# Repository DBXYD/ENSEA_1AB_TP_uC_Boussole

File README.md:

# ENSEA_1AB_TP_uC_Boussole

## TP

### PCB
Composants : 
* [NUCLEO-L476RG](https://www.st.com/en/evaluation-tools/nucleo-l476rg.html)
* [Magnétomètre 3 axes MMC5603 ADA5579](https://www.gotronic.fr/art-magnetometre-3-axes-mmc5603-ada5579-35829.htm)
* [GPS Tel0094](https://www.gotronic.fr/art-module-gps-tel0094-25732.htm)
* [Microcontroleur pour simulation trame NMEA STM32C011J4M6](https://fr.farnell.com/stmicroelectronics/stm32c011j4m6/mcu-arm-32-bits-48mhz-nsoic-8/dp/4138300)
* [Moteur pas à pas 17hs15-0404s](https://www.gotronic.fr/art-moteur-17hs15-0404s-18354.htm)
* [Driver de moteur pas à pas TMC2225](https://fr.farnell.com/trinamic/tmc2225-sa-t/driver-de-moteur-2a-40-a-125-c/dp/3690353?st=TMC2225-SA-T)
* [Codeur rotatif](https://fr.farnell.com/bourns/pec12r-2220f-s0024/encoder-quadrature-24ppr-15rpm/dp/4014827)
* [Ecran OLED 0.96"](https://www.gotronic.fr/art-afficheur-oled-0-96-i2c-oled01-31506.htm)
* [Mesure de courant NCS199A3RSQT2G](https://fr.farnell.com/on-semiconductor/ncs199a3rsqt2g/ampli-musure-de-cour-40khz-40/dp/2981170?st=NCS199A3RSQT2G)

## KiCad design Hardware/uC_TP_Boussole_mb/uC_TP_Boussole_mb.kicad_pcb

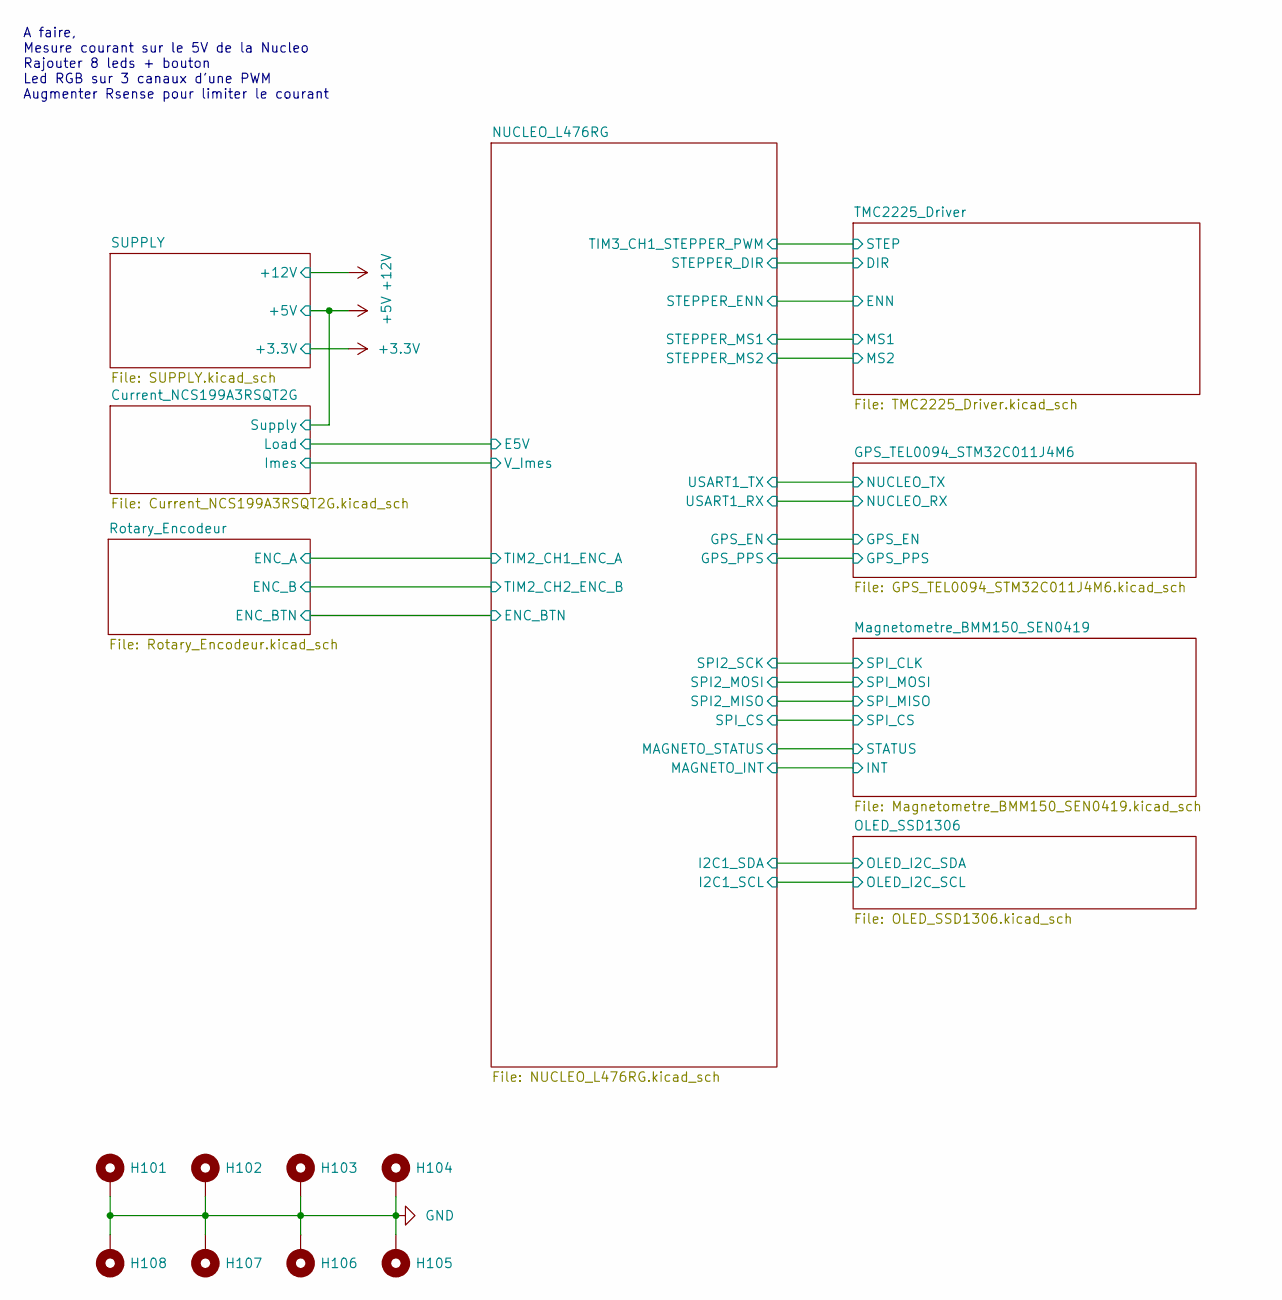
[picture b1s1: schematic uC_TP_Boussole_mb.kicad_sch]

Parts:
H101, H102, H103, H104, H105, H106, H107, H108: MountingHole_Pad; MountingHole_3.2mm_M3_Pad

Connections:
GND: H101.1, H102.1, H103.1, H104.1, H105.1, H106.1, H107.1, H108.1; also elsewhere on the board

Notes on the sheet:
A faire, Mesure courant sur le 5V de la Nucleo Rajouter 8 leds + bouton Led RGB sur 3 canaux d'une PWM Augmenter Rsense pour limiter le courant

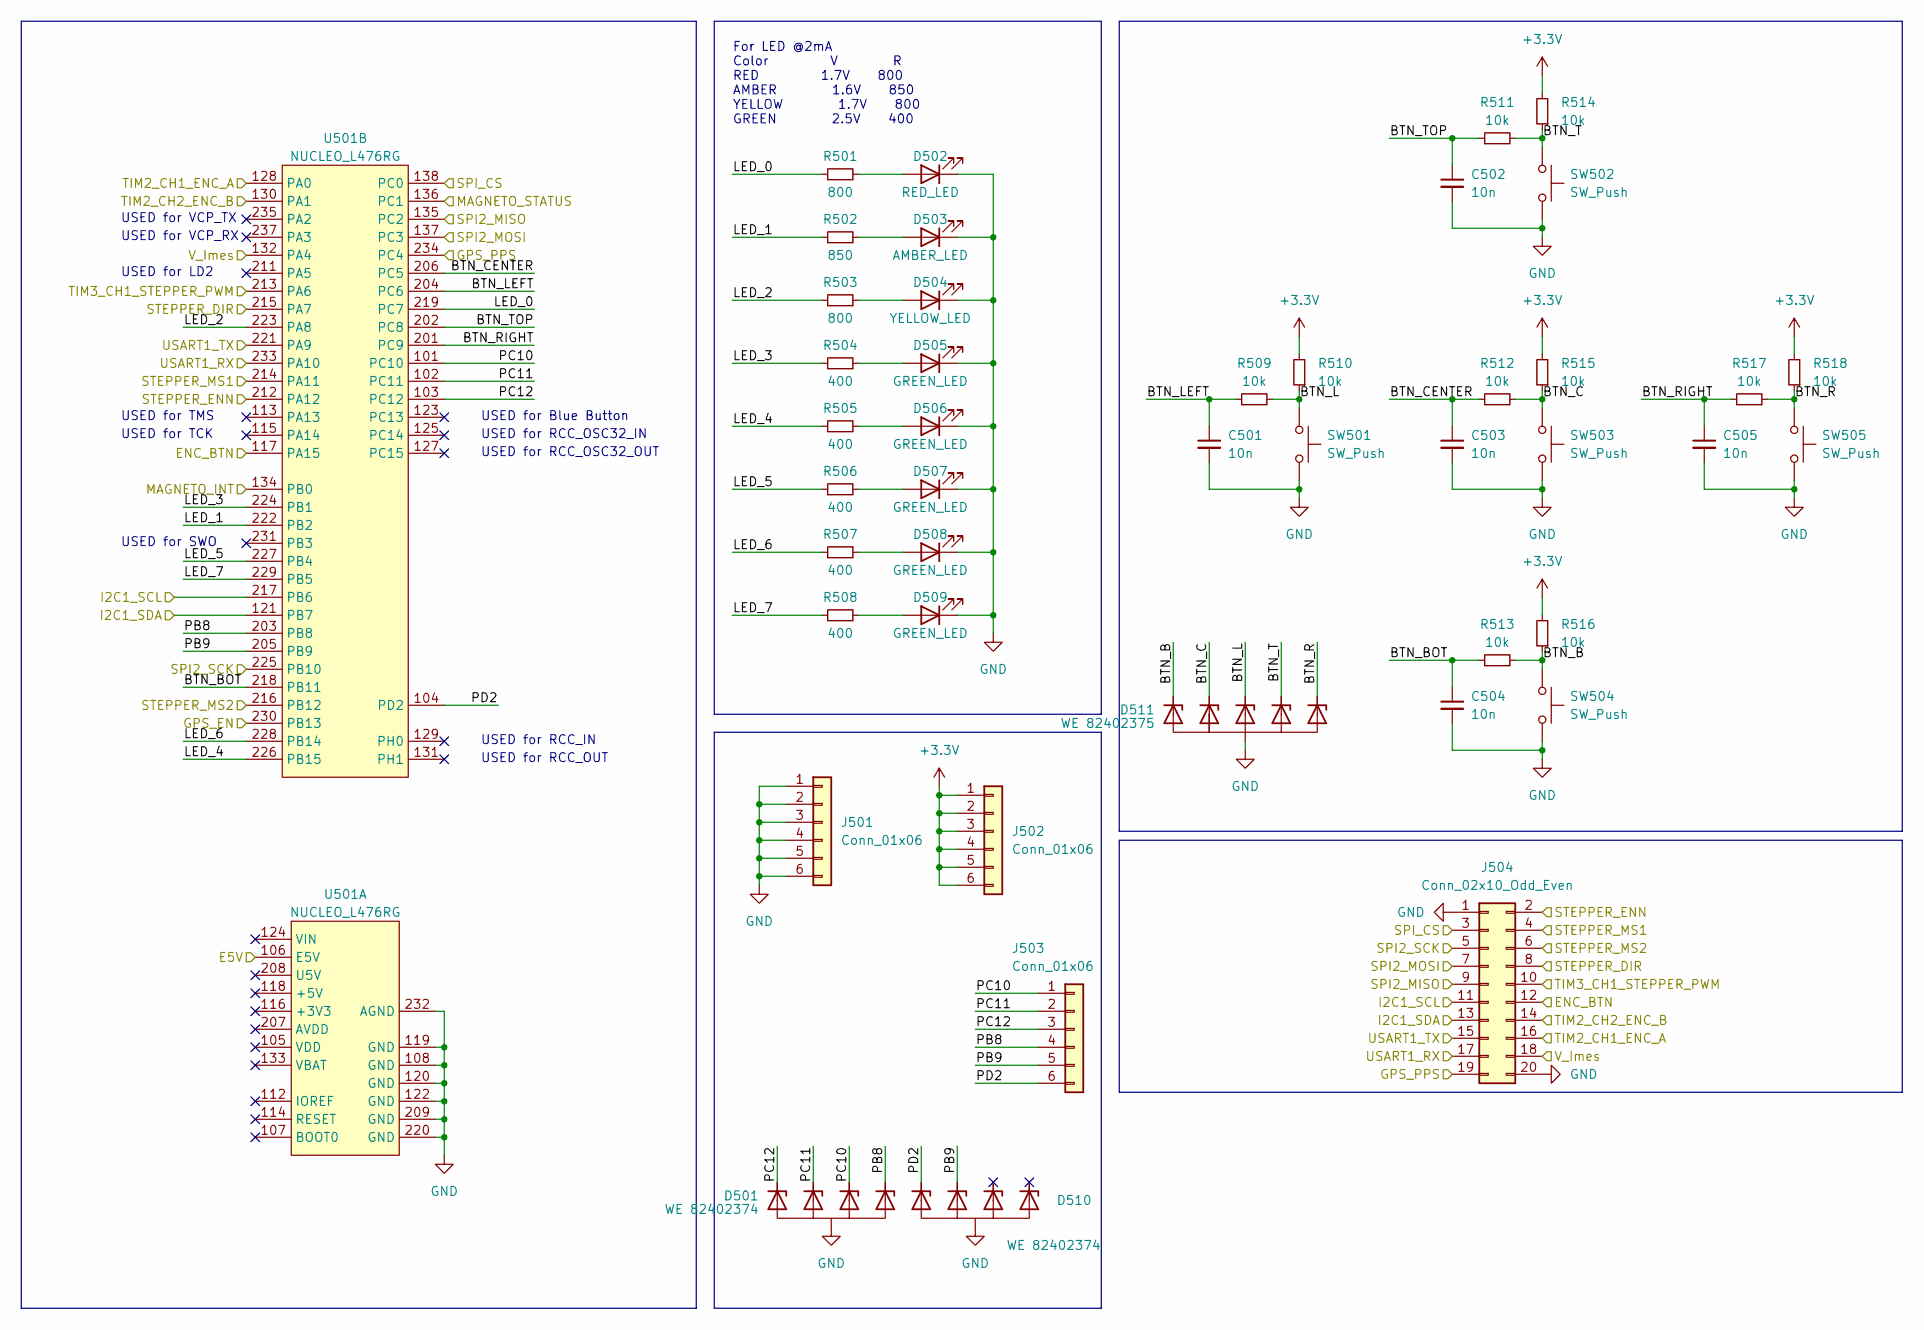
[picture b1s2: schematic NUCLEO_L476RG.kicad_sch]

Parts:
C501, C502, C503, C504, C505: 10n; C_0402_1005Metric
D501, D510: WE 82402374; SC70-5L; MPN WE 82402374
D502: RED_LED; LED_0603_1608Metric; MPN 150060RS55040
D503: AMBER_LED; LED_0603_1608Metric; MPN 150060AS55040
D504: YELLOW_LED; LED_0603_1608Metric; MPN 150060YS55040
D505, D506, D507, D508, D509: GREEN_LED; LED_0603_1608Metric; MPN 150060GS55040
D511: WE 82402375; SC70-6L; MPN WE 82402375
J501, J502, J503: Conn_01x06; PinHeader_1x06_P2.54mm_Vertical
J504: Conn_02x10_Odd_Even; PinHeader_2x10_P2.54mm_Vertical_SMD; MPN 61002021121
R501, R503: 800; R_0402_1005Metric
R502: 850; R_0402_1005Metric
R504, R505, R506, R507, R508: 400; R_0402_1005Metric
R509, R510, R511, R512, R513, R514, R515, R516, R517, R518: 10k; R_0402_1005Metric
SW501, SW502, SW503, SW504, SW505: SW_Push; SW_Push_1P1T_NO_6x6mm_H9.5mm
U501: NUCLEO_L476RG; ST_NUCLEO_64

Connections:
+3.3V: J502.1, J502.2, J502.3, J502.4, J502.5, J502.6, R510.2, R514.2, R515.2, R516.2, R518.2; also elsewhere on the board
/Current_NCS199A3RSQT2G/Imes: J504.18, U501.132 (PA4); also elsewhere on the board
/Current_NCS199A3RSQT2G/Load: U501.106 (E5V); also elsewhere on the board
/GPS_TEL0094_STM32C011J4M6/GPS_EN: U501.230 (PB13); also elsewhere on the board
/GPS_TEL0094_STM32C011J4M6/GPS_PPS: J504.19, U501.234 (PC4); also elsewhere on the board
/GPS_TEL0094_STM32C011J4M6/NUCLEO_RX: J504.17, U501.233 (PA10); also elsewhere on the board
/GPS_TEL0094_STM32C011J4M6/NUCLEO_TX: J504.15, U501.221 (PA9); also elsewhere on the board
/Magnetometre_BMM150_SEN0419/INT: U501.134 (PB0); also elsewhere on the board
/Magnetometre_BMM150_SEN0419/SPI_CLK: J504.5, U501.225 (PB10); also elsewhere on the board
/Magnetometre_BMM150_SEN0419/SPI_CS: J504.3, U501.138 (PC0); also elsewhere on the board
/Magnetometre_BMM150_SEN0419/SPI_MISO: J504.9, U501.135 (PC2); also elsewhere on the board
/Magnetometre_BMM150_SEN0419/SPI_MOSI: J504.7, U501.137 (PC3); also elsewhere on the board
/Magnetometre_BMM150_SEN0419/STATUS: U501.136 (PC1); also elsewhere on the board
/NUCLEO_L476RG/BTN_B: D511.6 (I/O), R513.2, R516.1, SW504.1
/NUCLEO_L476RG/BTN_BOT: C504.1, R513.1, U501.218 (PB11)
/NUCLEO_L476RG/BTN_C: D511.5 (I/O), R512.2, R515.1, SW503.1
/NUCLEO_L476RG/BTN_CENTER: C503.1, R512.1, U501.206 (PC5)
/NUCLEO_L476RG/BTN_L: D511.4 (I/O), R509.2, R510.1, SW501.1
/NUCLEO_L476RG/BTN_LEFT: C501.1, R509.1, U501.204 (PC6)
/NUCLEO_L476RG/BTN_R: D511.1 (I/O), R517.2, R518.1, SW505.1
/NUCLEO_L476RG/BTN_RIGHT: C505.1, R517.1, U501.201 (PC9)
/NUCLEO_L476RG/BTN_T: D511.3 (I/O), R511.2, R514.1, SW502.1
/NUCLEO_L476RG/BTN_TOP: C502.1, R511.1, U501.202 (PC8)
/NUCLEO_L476RG/ENC_BTN: J504.12, U501.117 (PA15); also elsewhere on the board
/NUCLEO_L476RG/I2C1_SCL: J504.11, U501.217 (PB6); also elsewhere on the board
/NUCLEO_L476RG/I2C1_SDA: J504.13, U501.121 (PB7); also elsewhere on the board
/NUCLEO_L476RG/LED_0: R501.1, U501.219 (PC7)
/NUCLEO_L476RG/LED_1: R502.1, U501.222 (PB2)
/NUCLEO_L476RG/LED_2: R503.1, U501.223 (PA8)
/NUCLEO_L476RG/LED_3: R504.1, U501.224 (PB1)
/NUCLEO_L476RG/LED_4: R505.1, U501.226 (PB15)
/NUCLEO_L476RG/LED_5: R506.1, U501.227 (PB4)
/NUCLEO_L476RG/LED_6: R507.1, U501.228 (PB14)
/NUCLEO_L476RG/LED_7: R508.1, U501.229 (PB5)
/NUCLEO_L476RG/PB8: D501.1 (I/O), J503.4, U501.203 (PB8)
/NUCLEO_L476RG/PB9: D510.4 (I/O), J503.5, U501.205 (PB9)
/NUCLEO_L476RG/PC10: D501.3 (I/O), J503.1, U501.101 (PC10)
/NUCLEO_L476RG/PC11: D501.4 (I/O), J503.2, U501.102 (PC11)
/NUCLEO_L476RG/PC12: D501.5 (I/O), J503.3, U501.103 (PC12)
/NUCLEO_L476RG/PD2: D510.5 (I/O), J503.6, U501.104 (PD2)
/NUCLEO_L476RG/STEPPER_DIR: J504.8, U501.215 (PA7); also elsewhere on the board
/NUCLEO_L476RG/STEPPER_ENN: J504.2, U501.212 (PA12); also elsewhere on the board
/NUCLEO_L476RG/STEPPER_MS1: J504.4, U501.214 (PA11); also elsewhere on the board
/NUCLEO_L476RG/STEPPER_MS2: J504.6, U501.216 (PB12); also elsewhere on the board
/NUCLEO_L476RG/TIM2_CH1_ENC_A: J504.16, U501.128 (PA0); also elsewhere on the board
/NUCLEO_L476RG/TIM2_CH2_ENC_B: J504.14, U501.130 (PA1); also elsewhere on the board
/NUCLEO_L476RG/TIM3_CH1_STEPPER_PWM: J504.10, U501.213 (PA6); also elsewhere on the board
GND: C501.2, C502.2, C503.2, C504.2, C505.2, D501.2 (GND), D502.1 (K), D503.1 (K), D504.1 (K), D505.1 (K), D506.1 (K), D507.1 (K), D508.1 (K), D509.1 (K), D510.2 (GND), D511.2 (GND), J501.1, J501.2, J501.3, J501.4, J501.5, J501.6, J504.1, J504.20, SW501.2, SW502.2, SW503.2, SW504.2, SW505.2, U501.108 (GND), U501.119 (GND), U501.120 (GND), U501.122 (GND), U501.209 (GND), U501.220 (GND), U501.232 (AGND); also elsewhere on the board
unnamed: D502.2 (A), R501.2
unnamed: D503.2 (A), R502.2
unnamed: D504.2 (A), R503.2
unnamed: D505.2 (A), R504.2
unnamed: D506.2 (A), R505.2
unnamed: D507.2 (A), R506.2
unnamed: D508.2 (A), R507.2
unnamed: D509.2 (A), R508.2

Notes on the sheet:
USED for SWO
USED for RCC_OUT
USED for VCP_RX
USED for RCC_OSC32_IN
USED for Blue Button
USED for RCC_IN
USED for RCC_OSC32_OUT
For LED @2mA Color V R RED 1.7V 800 AMBER 1.6V 850 YELLOW 1.7V 800 GREEN 2.5V 400
USED for TMS
USED for TCK
USED for VCP_TX
USED for LD2

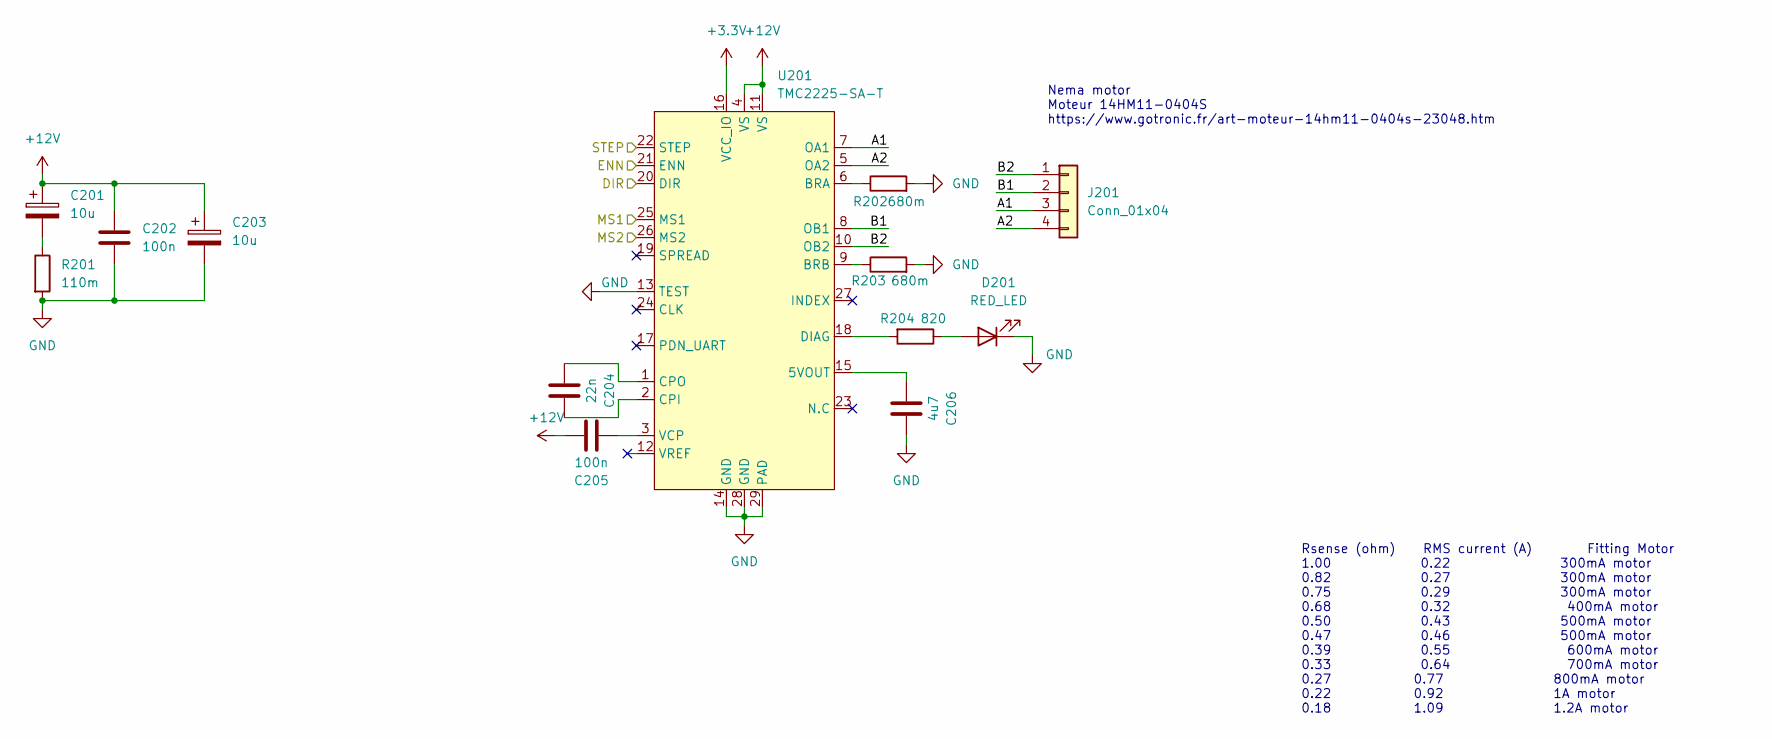
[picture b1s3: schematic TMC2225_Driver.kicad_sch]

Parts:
C201, C203: 10u; CP_Elec_4x5.7
C202, C205: 100n; C_0402_1005Metric
C204: 22n; C_0402_1005Metric
C206: 4u7; C_0402_1005Metric
D201: RED_LED; LED_0603_1608Metric; MPN 150060RS55040
J201: Conn_01x04; JST_XH_S4B-XH-A_1x04_P2.50mm_Horizontal
R201: 110m; R_0603_1608Metric_Pad0.98x0.95mm_HandSolder
R202, R203: 680m; R_1206_3216Metric_Pad1.30x1.75mm_HandSolder
R204: 820; R_0402_1005Metric
U201: TMC2225-SA-T; HTSSOP-28-1EP_4.4x9.7mm_P0.65mm_EP2.85x5.4mm_ThermalVias; MPN TMC2225-SA-T

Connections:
+3.3V: U201.16 (VCC_IO); also elsewhere on the board
+12V: C201.1, C202.1, C203.1, C205.1, U201.4 (VS), U201.11 (VS); also elsewhere on the board
/NUCLEO_L476RG/STEPPER_DIR: U201.20 (DIR); also elsewhere on the board
/NUCLEO_L476RG/STEPPER_ENN: U201.21 (ENN); also elsewhere on the board
/NUCLEO_L476RG/STEPPER_MS1: U201.25 (MS1); also elsewhere on the board
/NUCLEO_L476RG/STEPPER_MS2: U201.26 (MS2); also elsewhere on the board
/NUCLEO_L476RG/TIM3_CH1_STEPPER_PWM: U201.22 (STEP); also elsewhere on the board
/TMC2225_Driver/A1: J201.3, U201.7 (OA1)
/TMC2225_Driver/A2: J201.4, U201.5 (OA2)
/TMC2225_Driver/B1: J201.2, U201.8 (OB1)
/TMC2225_Driver/B2: J201.1, U201.10 (OB2)
GND: C202.2, C203.2, C206.1, D201.1 (K), R201.2, R202.2, R203.2, U201.13 (TEST), U201.14 (GND), U201.28 (GND), U201.29 (PAD); also elsewhere on the board
unnamed: C201.2, R201.1
unnamed: D201.2 (A), R204.1
unnamed: C206.2, U201.15 (5VOUT)
unnamed: R202.1, U201.6 (BRA)
unnamed: R203.1, U201.9 (BRB)
unnamed: C204.1, U201.2 (CPI)
unnamed: C204.2, U201.1 (CPO)
unnamed: R204.2, U201.18 (DIAG)
unnamed: C205.2, U201.3 (VCP)

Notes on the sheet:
Rsense (ohm) RMS current (A) Fitting Motor 1.00 0.22 300mA motor 0.82 0.27 300mA motor 0.75 0.29 300mA motor 0.68 0.32 400mA motor 0.50 0.43 500mA motor 0.47 0.46 500mA motor 0.39 0.55 600mA motor 0.33 0.64 700mA motor 0.27 0.77 800mA motor 0.22 0.92 1A motor 0.18 1.09 1.2A motor
Nema motor Moteur 14HM11-0404S https://www.gotronic.fr/art-moteur-14hm11-0404s-23048.htm

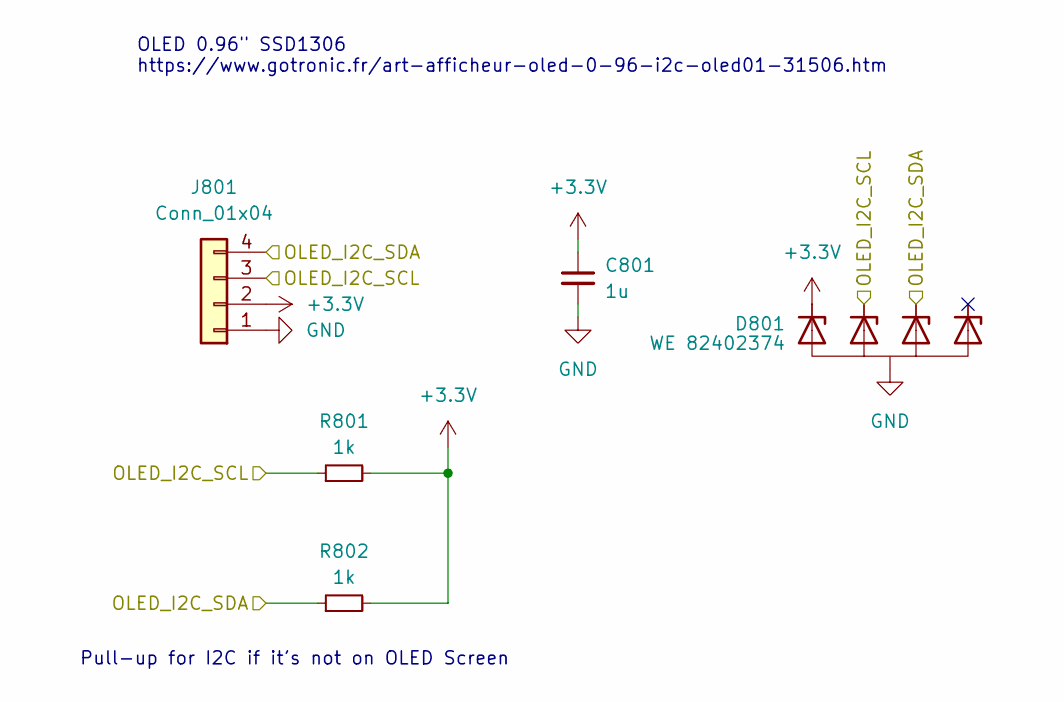
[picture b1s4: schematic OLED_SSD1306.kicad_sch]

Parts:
C801: 1u; C_0402_1005Metric
D801: WE 82402374; SC70-5L; MPN WE 82402374
J801: Conn_01x04; PinSocket_1x04_P2.54mm_Vertical
R801, R802: 1k; R_0402_1005Metric

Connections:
+3.3V: C801.1, D801.5 (I/O), J801.2, R801.2, R802.2; also elsewhere on the board
/NUCLEO_L476RG/I2C1_SCL: D801.4 (I/O), J801.3, R801.1; also elsewhere on the board
/NUCLEO_L476RG/I2C1_SDA: D801.3 (I/O), J801.4, R802.1; also elsewhere on the board
GND: C801.2, D801.2 (GND), J801.1; also elsewhere on the board

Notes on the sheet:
OLED 0.96" SSD1306 https://www.gotronic.fr/art-afficheur-oled-0-96-i2c-oled01-31506.htm
Pull-up for I2C if it's not on OLED Screen

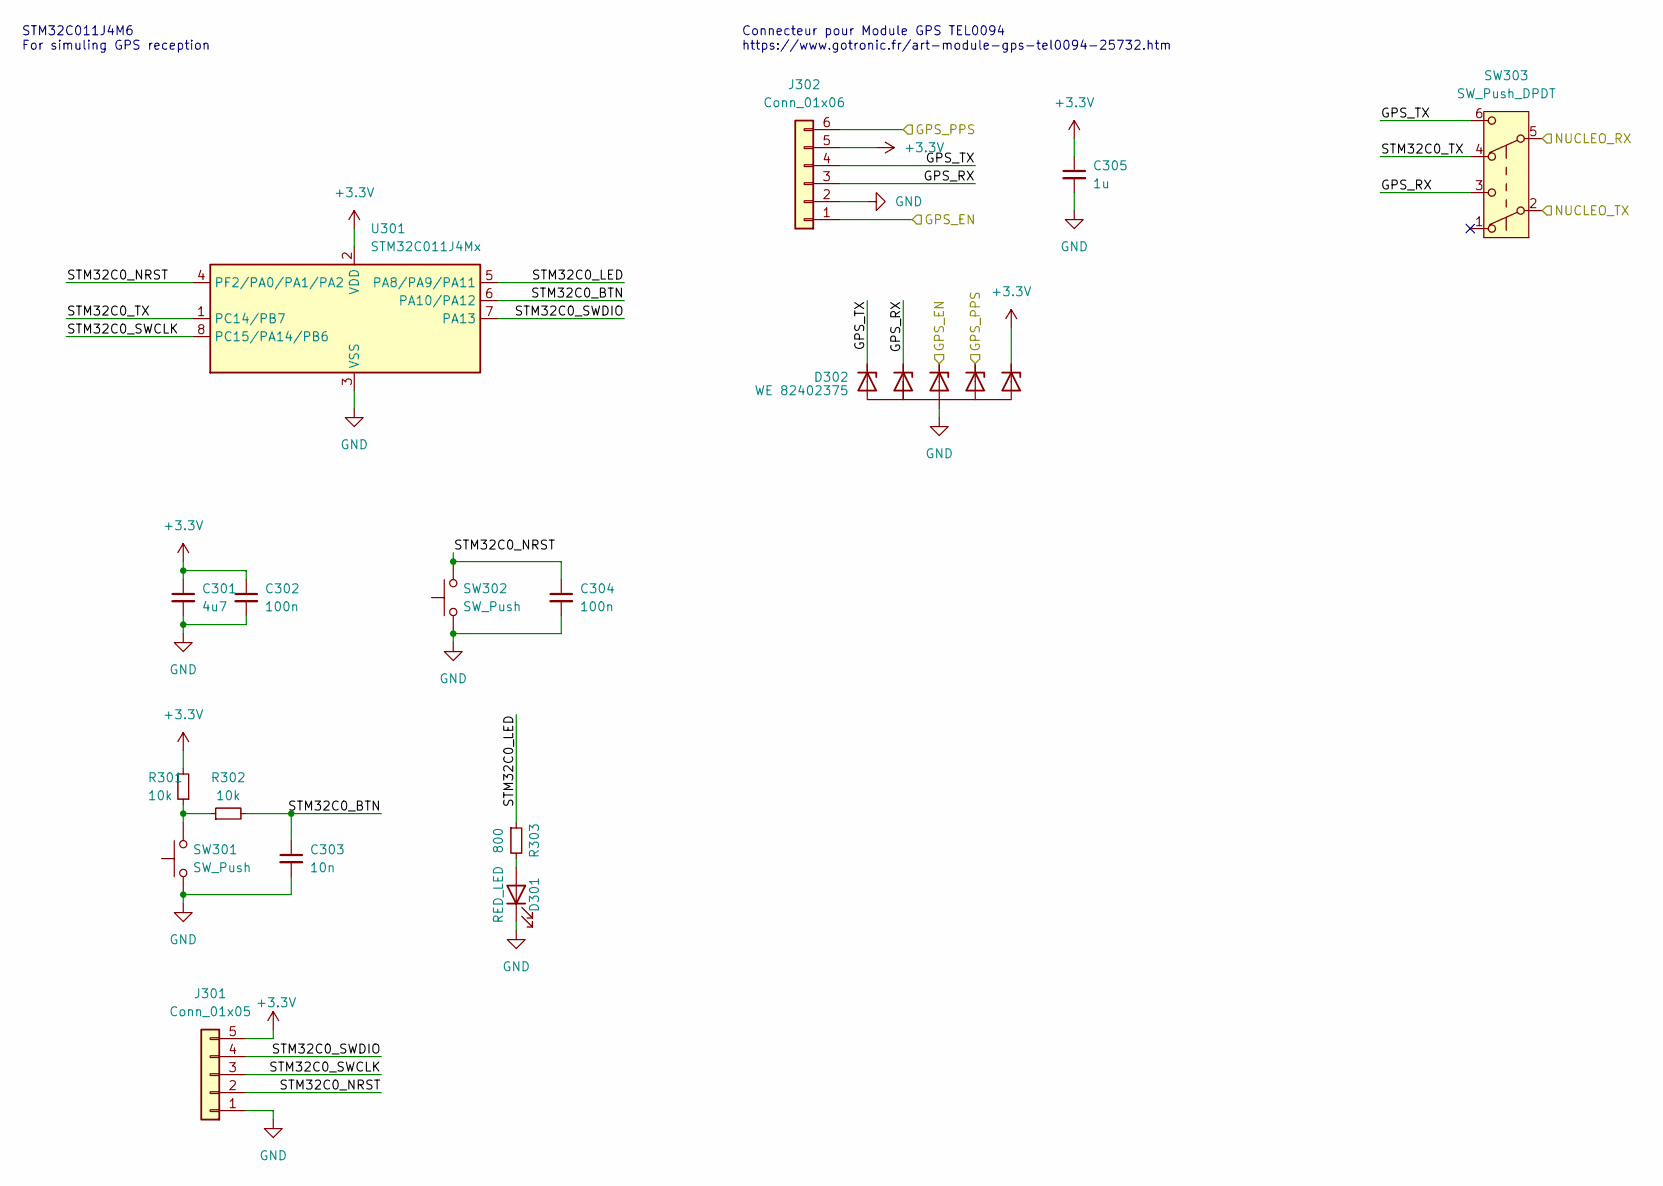
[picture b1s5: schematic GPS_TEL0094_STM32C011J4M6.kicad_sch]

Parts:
C301: 4u7; C_0402_1005Metric
C302, C304: 100n; C_0402_1005Metric
C303: 10n; C_0402_1005Metric
C305: 1u; C_0402_1005Metric
D301: RED_LED; LED_0603_1608Metric; MPN 150060RS55040
D302: WE 82402375; SC70-6L; MPN WE 82402375
J301: Conn_01x05; PinHeader_1x05_P2.54mm_Horizontal
J302: Conn_01x06; JST_XH_S6B-XH-A_1x06_P2.50mm_Horizontal
R301, R302: 10k; R_0402_1005Metric
R303: 800; R_0402_1005Metric
SW301, SW302: SW_Push; SW_Push_1P1T_NO_6x6mm_H9.5mm
SW303: SW_Push_DPDT; SW_DPDT_CK_JS202011JCQN
U301: STM32C011J4Mx; SOIC-8_3.9x4.9mm_P1.27mm

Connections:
+3.3V: C301.1, C302.1, C305.1, D302.1 (I/O), J301.5, J302.5, R301.2, U301.2 (VDD); also elsewhere on the board
/GPS_TEL0094_STM32C011J4M6/GPS_EN: D302.4 (I/O), J302.1; also elsewhere on the board
/GPS_TEL0094_STM32C011J4M6/GPS_PPS: D302.3 (I/O), J302.6; also elsewhere on the board
/GPS_TEL0094_STM32C011J4M6/GPS_RX: D302.5 (I/O), J302.3, SW303.3 (C)
/GPS_TEL0094_STM32C011J4M6/GPS_TX: D302.6 (I/O), J302.4, SW303.6 (C)
/GPS_TEL0094_STM32C011J4M6/NUCLEO_RX: SW303.5 (B); also elsewhere on the board
/GPS_TEL0094_STM32C011J4M6/NUCLEO_TX: SW303.2 (B); also elsewhere on the board
/GPS_TEL0094_STM32C011J4M6/STM32C0_BTN: C303.1, R302.2, U301.6 (PA10/PA12)
/GPS_TEL0094_STM32C011J4M6/STM32C0_LED: R303.1, U301.5 (PA8/PA9/PA11)
/GPS_TEL0094_STM32C011J4M6/STM32C0_NRST: C304.1, J301.2, SW302.2, U301.4 (PF2/PA0/PA1/PA2)
/GPS_TEL0094_STM32C011J4M6/STM32C0_SWCLK: J301.3, U301.8 (PC15/PA14/PB6)
/GPS_TEL0094_STM32C011J4M6/STM32C0_SWDIO: J301.4, U301.7 (PA13)
/GPS_TEL0094_STM32C011J4M6/STM32C0_TX: SW303.4 (A), U301.1 (PC14/PB7)
GND: C301.2, C302.2, C303.2, C304.2, C305.2, D301.1 (K), D302.2 (GND), J301.1, J302.2, SW301.1, SW302.1, U301.3 (VSS); also elsewhere on the board
unnamed: D301.2 (A), R303.2
unnamed: R301.1, R302.1, SW301.2

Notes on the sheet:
Connecteur pour Module GPS TEL0094 https://www.gotronic.fr/art-module-gps-tel0094-25732.htm
STM32C011J4M6 For simuling GPS reception

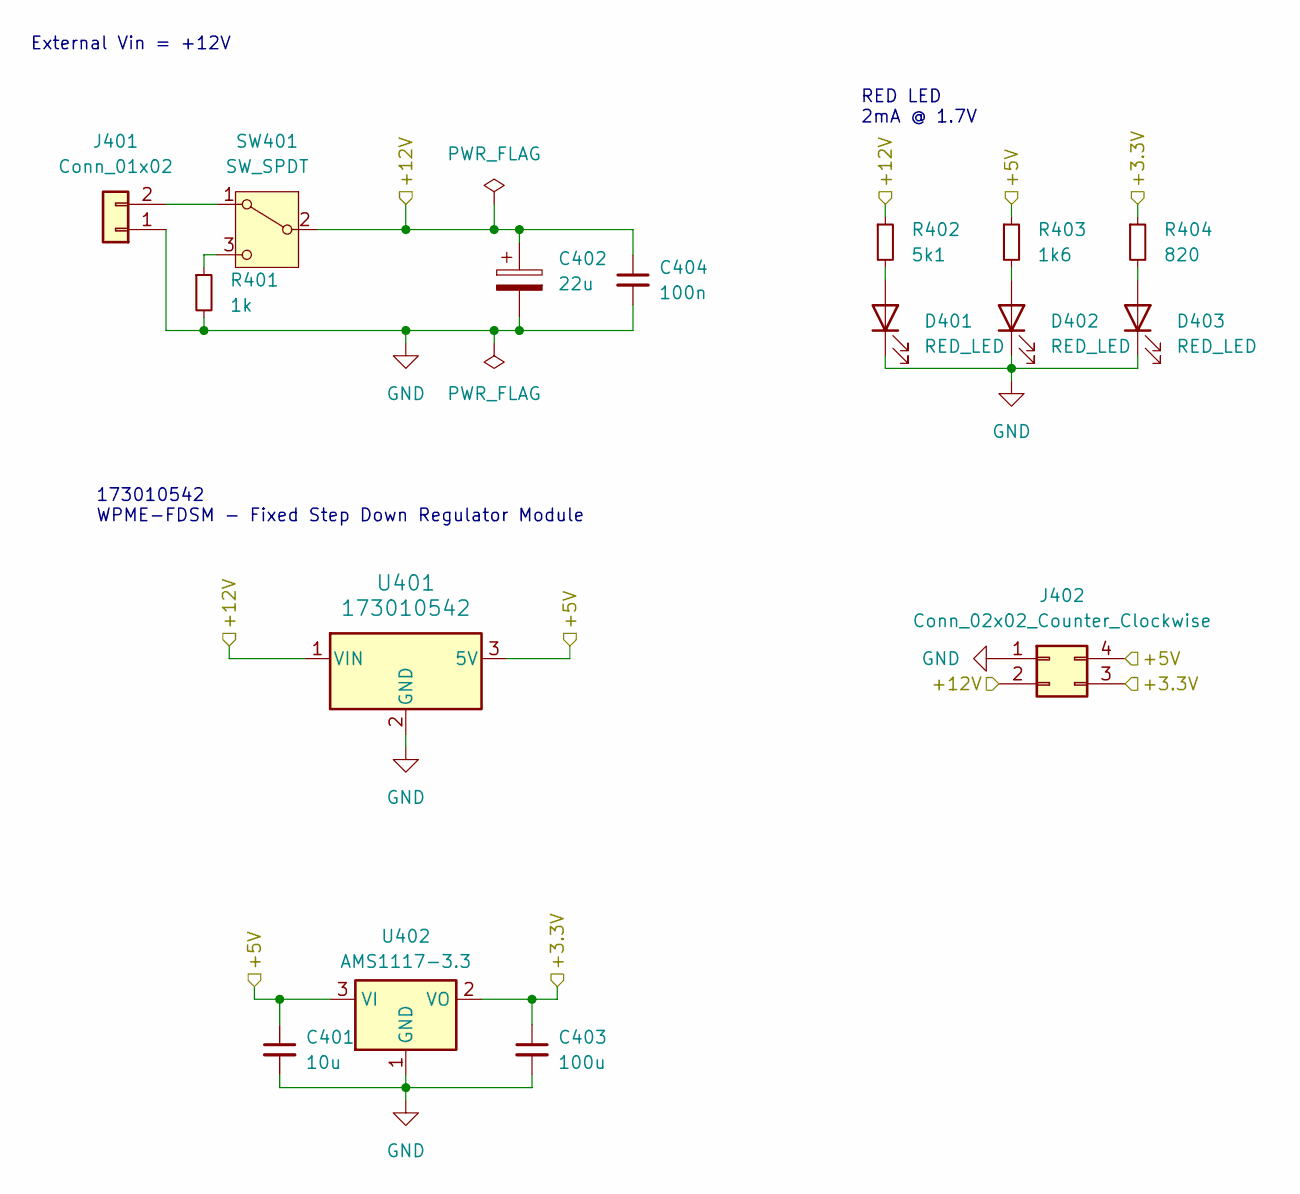
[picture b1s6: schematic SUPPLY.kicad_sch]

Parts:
C401: 10u; C_0402_1005Metric
C402: 22u; CP_Elec_5x5.4; MPN 865060442002
C403: 100u; C_0402_1005Metric
C404: 100n; C_0402_1005Metric
D401, D402, D403: RED_LED; LED_0603_1608Metric; MPN 150060RS55040
J401: Conn_01x02; JST_XH_S2B-XH-A_1x02_P2.50mm_Horizontal
J402: Conn_02x02_Counter_Clockwise; PinHeader_2x02_P2.54mm_Vertical_SMD; MPN 61000421121
R401: 1k; R_0805_2012Metric
R402: 5k1; R_0402_1005Metric
R403: 1k6; R_0402_1005Metric
R404: 820; R_0402_1005Metric
SW401: SW_SPDT; 472121020311; MPN 472121020311
U401: 173010542; 173010xxx
U402: AMS1117-3.3; SOT-223-3_TabPin2

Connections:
+3.3V: C403.1, J402.3, R404.1, U402.2 (VO); also elsewhere on the board
+5V: C401.1, J402.4, R403.1, U401.3 (5V), U402.3 (VI); also elsewhere on the board
+12V: C402.1, C404.1, J402.2, R402.1, SW401.2 (B), U401.1 (VIN); also elsewhere on the board
GND: C401.2, C402.2, C403.2, C404.2, D401.1 (K), D402.1 (K), D403.1 (K), J401.1, J402.1, R401.2, U401.2 (GND), U402.1 (GND); also elsewhere on the board
unnamed: D401.2 (A), R402.2
unnamed: D402.2 (A), R403.2
unnamed: D403.2 (A), R404.2
unnamed: J401.2, SW401.1 (A)
unnamed: R401.1, SW401.3 (C)

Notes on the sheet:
RED LED 2mA @ 1.7V
173010542 WPME-FDSM - Fixed Step Down Regulator Module
External Vin = +12V

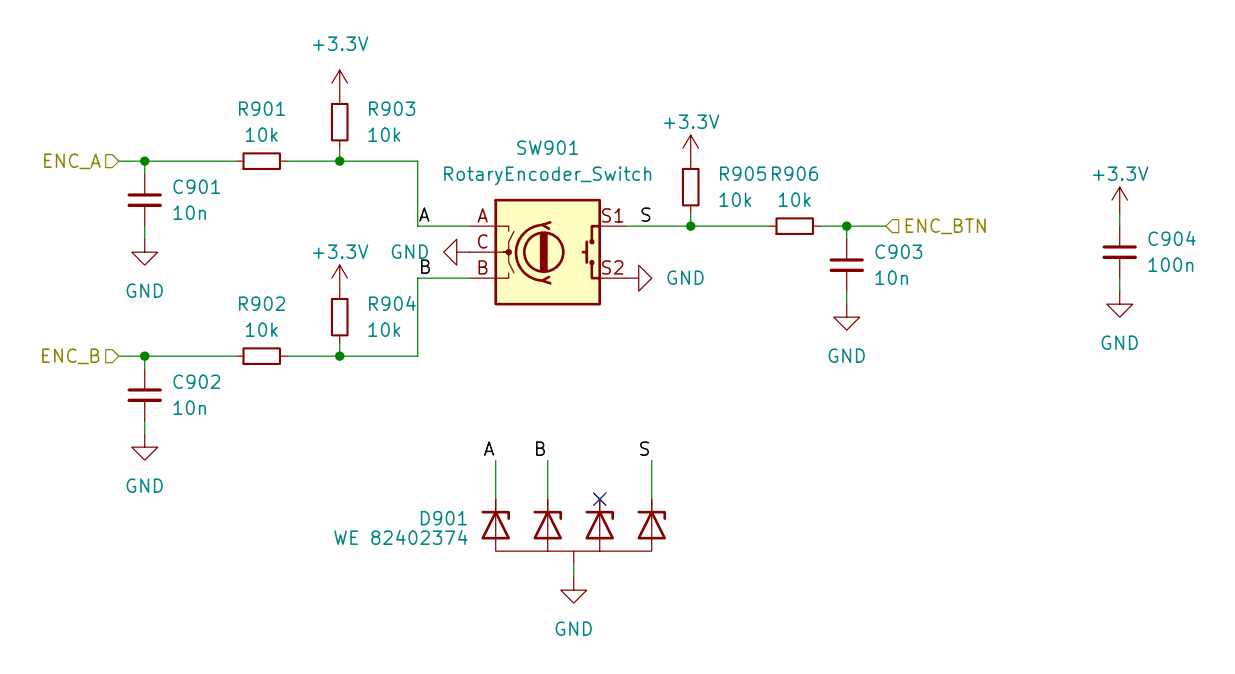
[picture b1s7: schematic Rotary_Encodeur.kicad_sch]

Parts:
C901, C902, C903: 10n; C_0402_1005Metric
C904: 100n; C_0402_1005Metric
D901: WE 82402374; SC70-5L; MPN WE 82402374
R901, R902, R903, R904, R905, R906: 10k; R_0402_1005Metric
SW901: RotaryEncoder_Switch; 482016514001_Mechanical_Incremental_Encoder_Switch; MPN 482016514001

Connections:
+3.3V: C904.1, R903.1, R904.1, R905.1; also elsewhere on the board
/NUCLEO_L476RG/ENC_BTN: C903.1, R906.2; also elsewhere on the board
/NUCLEO_L476RG/TIM2_CH1_ENC_A: C901.1, R901.1; also elsewhere on the board
/NUCLEO_L476RG/TIM2_CH2_ENC_B: C902.1, R902.1; also elsewhere on the board
/Rotary_Encodeur/A: D901.5 (I/O), R901.2, R903.2, SW901.A
/Rotary_Encodeur/B: D901.4 (I/O), R902.2, R904.2, SW901.B
/Rotary_Encodeur/S: D901.1 (I/O), R905.2, R906.1, SW901.S1
GND: C901.2, C902.2, C903.2, C904.2, D901.2 (GND), SW901.C, SW901.S2; also elsewhere on the board

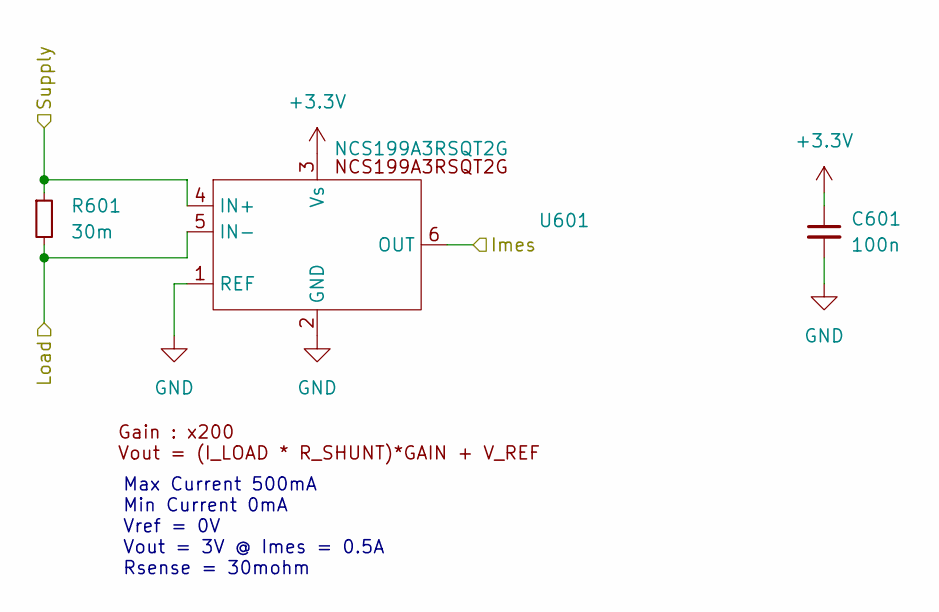
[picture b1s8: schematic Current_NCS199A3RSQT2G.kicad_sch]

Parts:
C601: 100n; C_0402_1005Metric
R601: 30m; R_0402_1005Metric
U601: NCS199A3RSQT2G; SOT-363_SC-70-6; MPN NCS199A3RSQT2G

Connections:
+3.3V: C601.1, U601.3 (Vs); also elsewhere on the board
+5V: R601.1, U601.4 (IN+); also elsewhere on the board
/Current_NCS199A3RSQT2G/Imes: U601.6 (OUT); also elsewhere on the board
/Current_NCS199A3RSQT2G/Load: R601.2, U601.5 (IN-); also elsewhere on the board
GND: C601.2, U601.1 (REF), U601.2 (GND); also elsewhere on the board

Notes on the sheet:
Max Current 500mA Min Current 0mA Vref = 0V Vout = 3V @ Imes = 0.5A Rsense = 30mohm

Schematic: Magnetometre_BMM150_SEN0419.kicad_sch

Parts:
C701: 1u; C_0402_1005Metric
D701, D702: WE 82402374; SC70-5L; MPN WE 82402374
J701: Conn_01x09; JST_XH_S9B-XH-A_1x09_P2.50mm_Horizontal

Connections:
+3.3V: C701.1, D701.3 (I/O), J701.1; also elsewhere on the board
/Magnetometre_BMM150_SEN0419/INT: D702.5 (I/O), J701.9; also elsewhere on the board
/Magnetometre_BMM150_SEN0419/SPI_CLK: D701.4 (I/O), J701.3; also elsewhere on the board
/Magnetometre_BMM150_SEN0419/SPI_CS: D702.3 (I/O), J701.6; also elsewhere on the board
/Magnetometre_BMM150_SEN0419/SPI_MISO: D702.1 (I/O), J701.5; also elsewhere on the board
/Magnetometre_BMM150_SEN0419/SPI_MOSI: D701.5 (I/O), J701.4; also elsewhere on the board
/Magnetometre_BMM150_SEN0419/STATUS: D702.4 (I/O), J701.8; also elsewhere on the board
GND: C701.2, D701.2 (GND), D702.2 (GND), J701.2, J701.7; also elsewhere on the board

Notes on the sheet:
Magnétomètre 3 axes BMM150 SEN0419
